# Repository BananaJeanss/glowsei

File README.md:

# glowsei

Ralsei-shaped PCB with LEDs that turn on automatically in the dark, and a button to override and turn on all LEDs, and a mini motor disc as well.

## Bill Of Materials (BOM)

| Component                | Quantity |
| ------------------------ | -------- |
| 5mm LEDs                 | 5        |
| Photoresistor (GL5528)   | 1        |
| 220Ω Resistors           | 5        |
| 47kΩ Resistors           | 2        |
| NPN Transistor (2N3904)  | 1        |
| Mini Motor Disc/DC Motor | 1        |
| Push Button (6mm THT)    | 1        |
| CR2032 Battery Cell      | 1        |

## Images

| Image | Description |
| ----- | ----------- |
|  | Front 3D View |
|  | Back 3D View |
|  | PCB |
|  | Schematic |

---
Made for <https://solder.hackclub.com/>

`U08R49H9VRV` on slack

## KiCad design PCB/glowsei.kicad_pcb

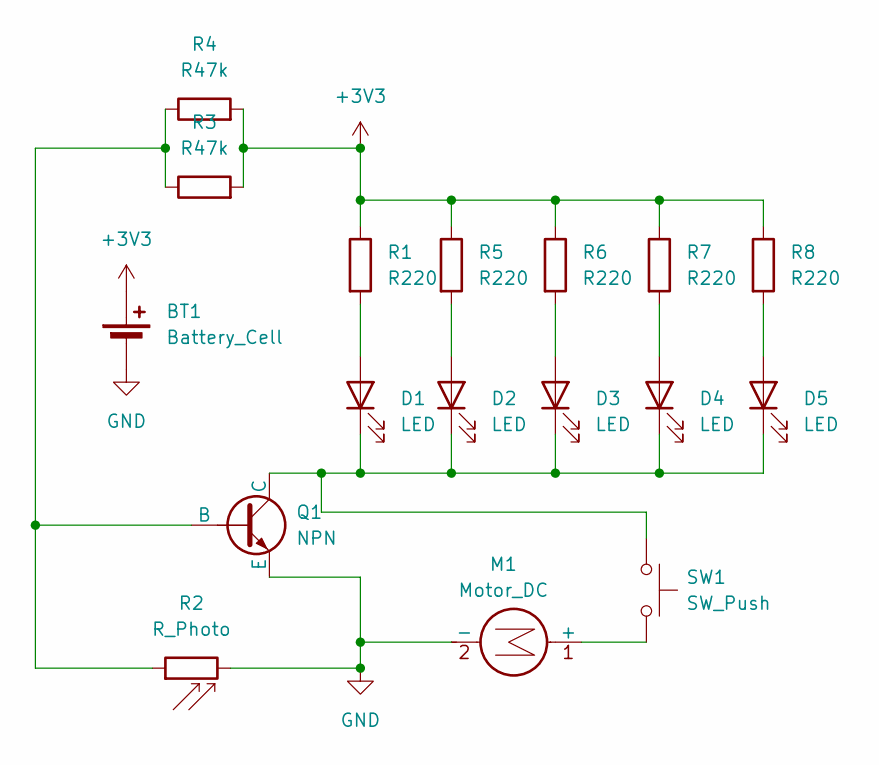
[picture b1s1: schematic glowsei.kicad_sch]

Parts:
BT1: Battery_Cell; BatteryHolder_Keystone_3034_1x20mm
D1, D2, D3, D4, D5: LED; LED_D5.0mm
M1: Motor_DC; PinHeader_1x02_P2.54mm_Vertical
Q1: NPN; TO-92L_HandSolder
R1, R5, R6, R7, R8: R220; R_Axial_DIN0207_L6.3mm_D2.5mm_P7.62mm_Horizontal
R2: R_Photo; R_LDR_5.1x4.3mm_P3.4mm_Vertical
R3, R4: R47k; R_Axial_DIN0207_L6.3mm_D2.5mm_P7.62mm_Horizontal
SW1: SW_Push; SW_PUSH_6mm

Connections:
+3V3: BT1.1 (+), R1.1, R3.2, R4.2, R5.1, R6.1, R7.1, R8.1
GND: BT1.2 (-), M1.2 (-), Q1.3 (E), R2.2
unnamed: D1.2 (A), R1.2
unnamed: D1.1 (K), D2.1 (K), D3.1 (K), D4.1 (K), D5.1 (K), Q1.1 (C), SW1.1
unnamed: D2.2 (A), R5.2
unnamed: D3.2 (A), R6.2
unnamed: D4.2 (A), R7.2
unnamed: D5.2 (A), R8.2
unnamed: M1.1 (+), SW1.2
unnamed: Q1.2 (B), R2.1, R3.1, R4.1

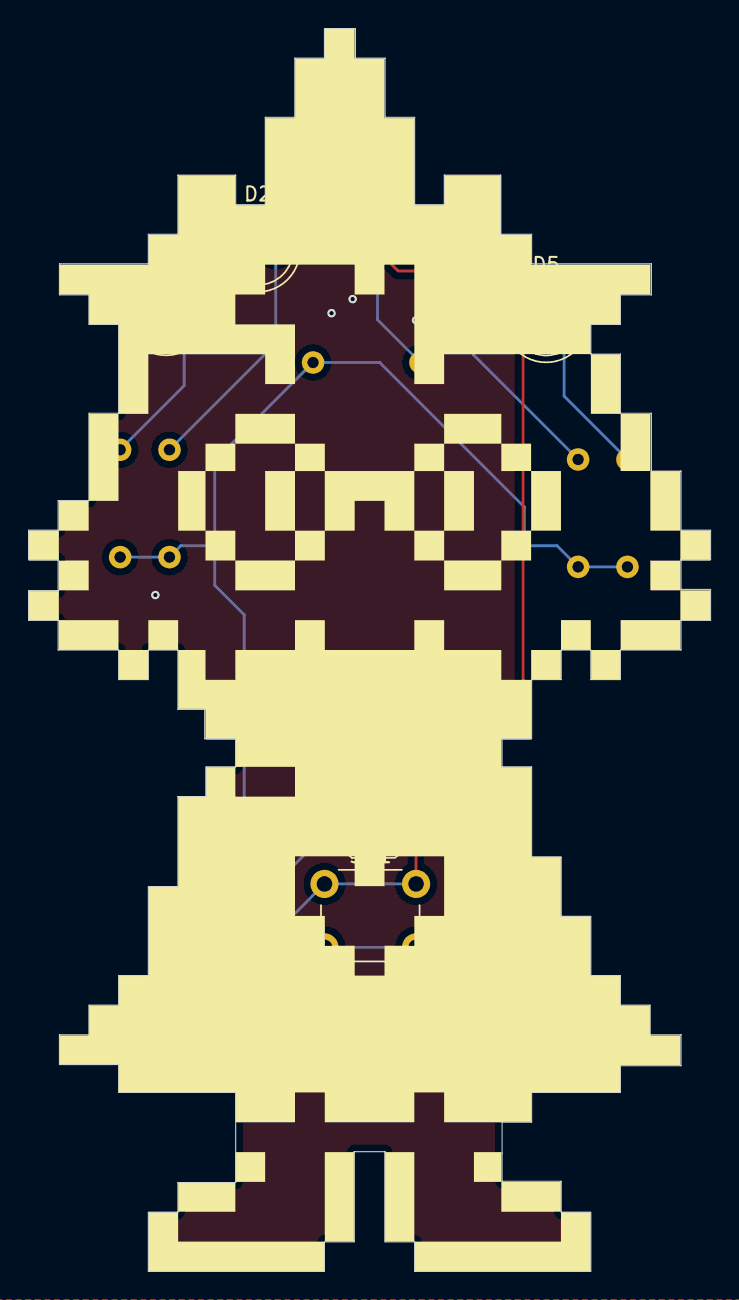
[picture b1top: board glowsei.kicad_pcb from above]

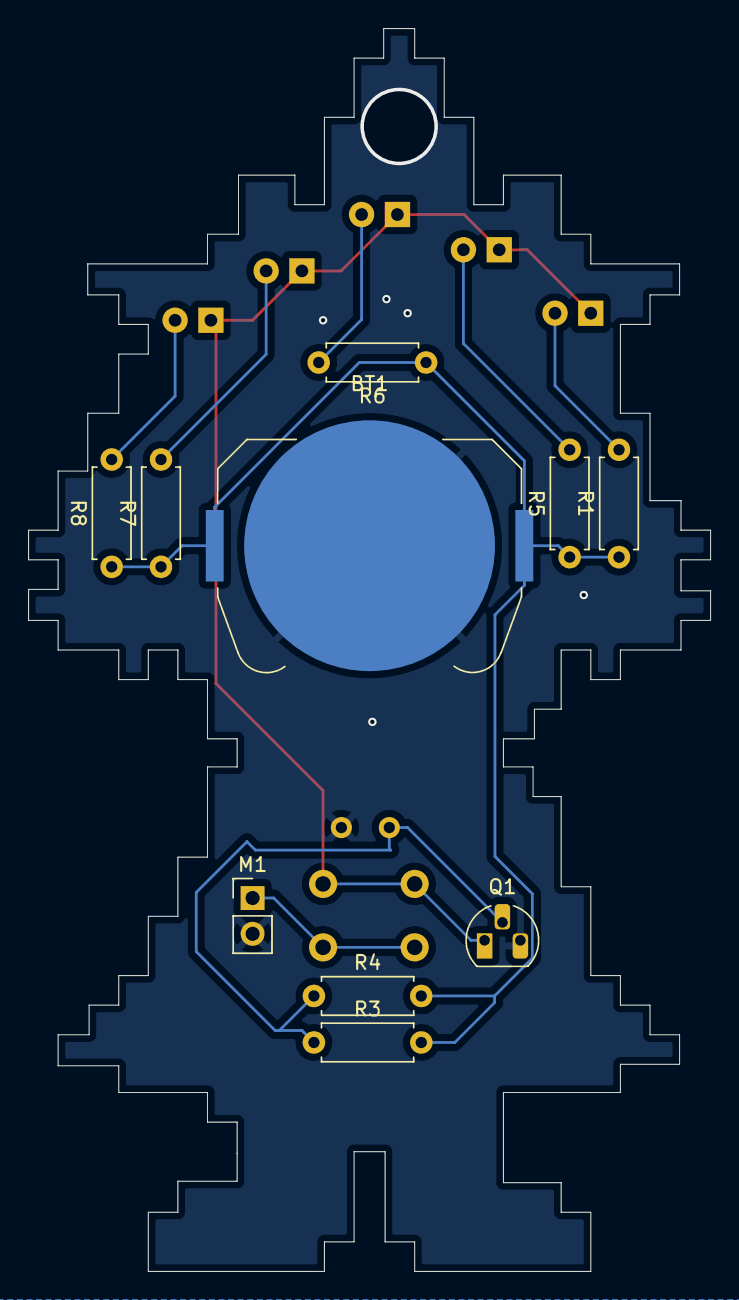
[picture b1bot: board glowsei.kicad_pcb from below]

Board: 2 copper layers, 48.4 x 88.2 mm, 17 parts (10 on the bottom side), 10 nets.

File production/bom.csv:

Designator,Footprint,Quantity,Value,LCSC Part #
BT1,BatteryHolder_Keystone_3034_1x20mm,1,Battery_Cell,
"D1, D2, D3, D4, D5",LED_D5.0mm,5,LED,
M1,PinHeader_1x02_P2.54mm_Vertical,1,Motor_DC,
Q1,TO-92L_HandSolder,1,NPN,
"R1, R5, R6, R7, R8",R_Axial_DIN0207_L6.3mm_D2.5mm_P7.62mm_Horizontal,5,R220,
R2,R_LDR_5.1x4.3mm_P3.4mm_Vertical,1,R_Photo,
"R3, R4",R_Axial_DIN0207_L6.3mm_D2.5mm_P7.62mm_Horizontal,2,R47k,
SW1,SW_PUSH_6mm,1,SW_Push,
